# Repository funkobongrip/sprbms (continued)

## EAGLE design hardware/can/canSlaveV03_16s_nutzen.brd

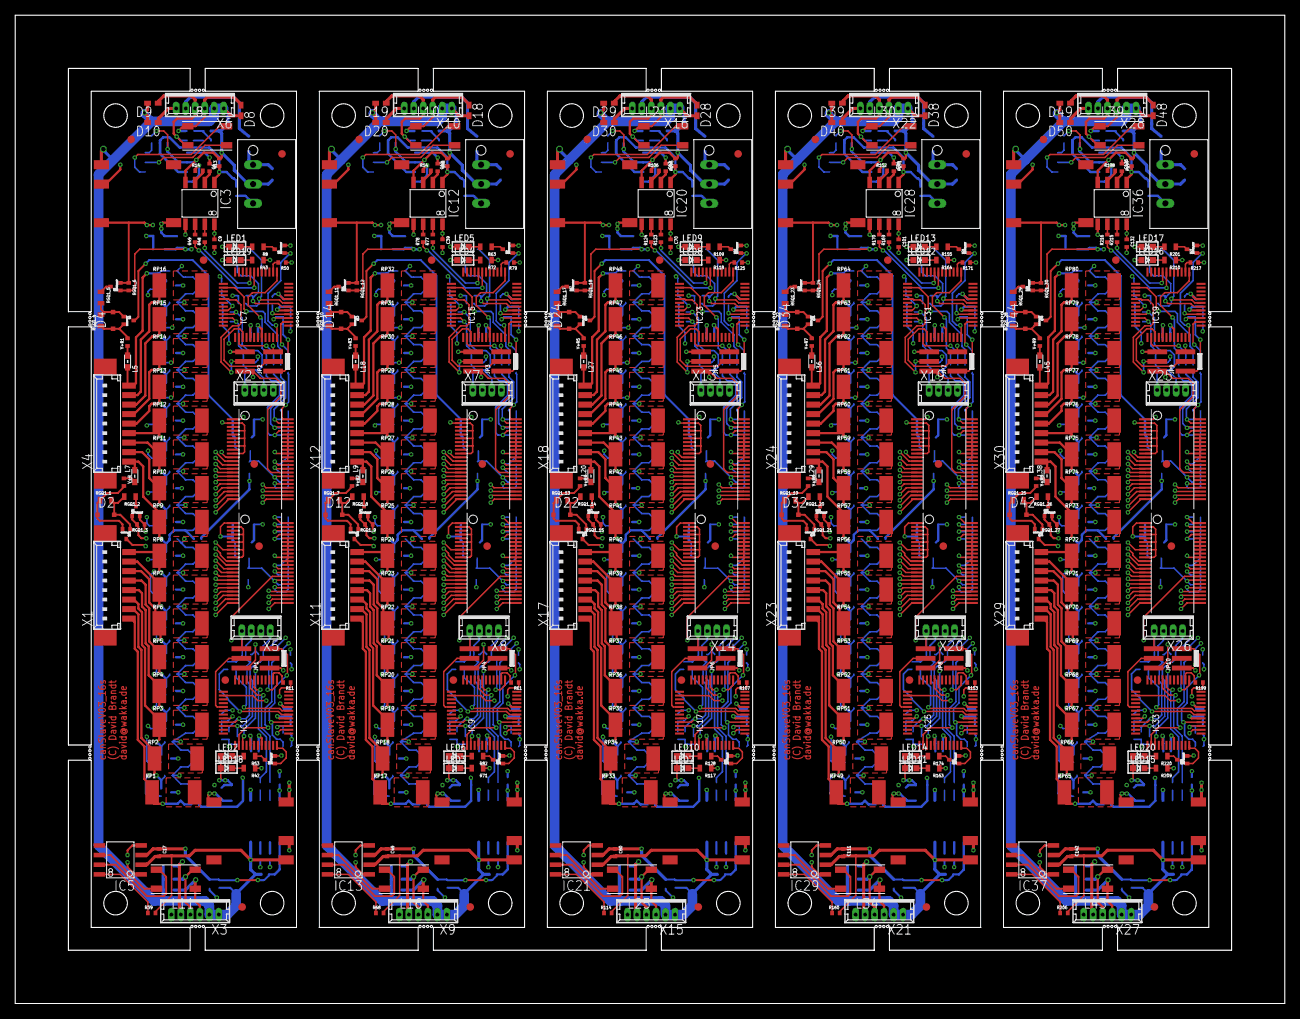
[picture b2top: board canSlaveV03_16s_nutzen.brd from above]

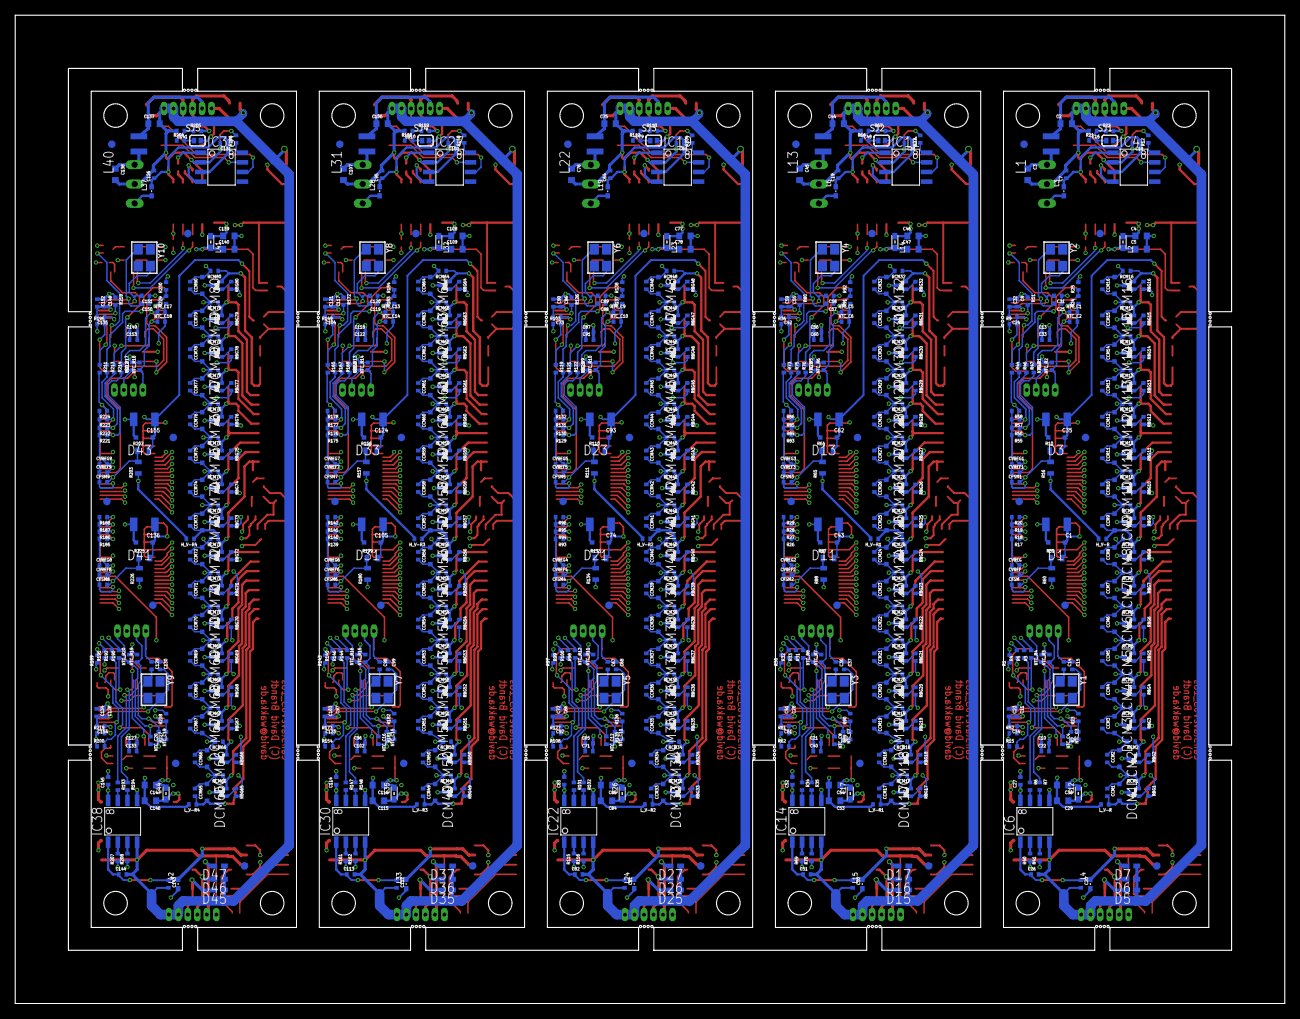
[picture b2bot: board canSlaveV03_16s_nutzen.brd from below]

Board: 4 copper layers, 167.0 x 130.0 mm, 1310 parts (905 on the bottom side), 895 nets.

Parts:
C1, C35, C43, C62, C74, C93, C105, C124, C136, C155: 10u,50V; C1206
C2, C3, C4, C5, C29, C30, C44, C45, C46, C47, C53, C54, C75, C76, C77, C78, C84, C85, C106, C107, C108, C109, C115, C116, C137, C138, C139, C140, C146, C147: 10u,50V; C0603
C6, C9, C12, C17, C18, C22, C23, C24, C26, C27, C32, C33, C34, C38, C39, C40, C41, C42, C49, C51, C52, C59, C60, C61, C63, C69, C70, C71, C72, C73, C80, C82, C83, C90, C91, C92, C94, C100, C101, C102, C103, C104, C111, C113, C114, C121, C122, C123, C125, C131, C132, C133, C134, C135, C142, C144, C145, C152, C153, C154: 100n; C0402
C7, C19, C20, C50, C64, C81, C95, C112, C126, C143: 1u; C0402
C8, C10, C11, C13, C21, C28, C55, C56, C65, C66, C86, C87, C96, C97, C117, C118, C127, C128, C148, C149: 10n; C0402
C14, C15, C25, C31, C36, C37, C57, C58, C67, C68, C88, C89, C98, C99, C119, C120, C129, C130, C150, C151: 18p; C0402
C16, C48, C79, C110, C141: 47n; C0402
CCM1, CCM2, CCM3, CCM4, CCM5, CCM6, CCM7, CCM8, CCM9, CCM10, CCM11, CCM12, CCM13, CCM14, CCM15, CCM16, CCM17, CCM18, CCM19, CCM20, CCM21, CCM22, CCM23, CCM24, CCM25, CCM26, CCM27, CCM28, CCM29, CCM30, CCM31, CCM32, CCM33, CCM34, CCM35, CCM36, CCM37, CCM38, CCM39, CCM40, CCM41, CCM42, CCM43, CCM44, CCM45, CCM46, CCM47, CCM48, CCM49, CCM50, CCM51, CCM52, CCM53, CCM54, CCM55, CCM56, CCM57, CCM58, CCM59, CCM60, CCM61, CCM62, CCM63, CCM64, CCM65, CCM66, CCM67, CCM68, CCM69, CCM70, CCM71, CCM72, CCM73, CCM74, CCM75, CCM76, CCM77, CCM78, CCM79, CCM80: 100n; C0402
CFSM, CFSM1, CFSM2, CFSM3, CFSM4, CFSM5, CFSM6, CFSM7, CFSM8, CFSM9: 1u; C0402
CVREF, CVREF1, CVREF2, CVREF3, CVREF4, CVREF5, CVREF6, CVREF7, CVREF8, CVREF9: 1u; C0402
CVREG, CVREG1, CVREG2, CVREG3, CVREG4, CVREG5, CVREG6, CVREG7, CVREG8, CVREG9: 1u; C0402
D1, D3, D11, D13, D21, D23, D31, D33, D41, D43: 40V; SOD323-R
D2, D4, D12, D14, D22, D24, D32, D34, D42, D44: 12V; SOD323-R
D5, D6, D7, D8, D9, D10, D15, D16, D17, D18, D19, D20, D25, D26, D27, D28, D29, D30, D35, D36, D37, D38, D39, D40, D45, D46, D47, D48, D49, D50: WE-VE_0402; WESURGE_0402
DCDC1, DCDC2, DCDC3, DCDC4, DCDC5, DCDC6, DCDC7, DCDC8, DCDC9, DCDC10: TES 1-0510; ISF
DCIN, DCIN1, DCIN2, DCIN3, DCIN4: TSR 1-2450; TSR1
DCM1, DCM2, DCM3, DCM4, DCM5, DCM6, DCM7, DCM8, DCM9, DCM10, DCM11, DCM12, DCM13, DCM14, DCM15, DCM16, DCM17, DCM18, DCM19, DCM20, DCM21, DCM22, DCM23, DCM24, DCM25, DCM26, DCM27, DCM28, DCM29, DCM30, DCM31, DCM32, DCM33, DCM34, DCM35, DCM36, DCM37, DCM38, DCM39, DCM40, DCM41, DCM42, DCM43, DCM44, DCM45, DCM46, DCM47, DCM48, DCM49, DCM50, DCM51, DCM52, DCM53, DCM54, DCM55, DCM56, DCM57, DCM58, DCM59, DCM60, DCM61, DCM62, DCM63, DCM64, DCM65, DCM66, DCM67, DCM68, DCM69, DCM70, DCM71, DCM72, DCM73, DCM74, DCM75, DCM76, DCM77, DCM78, DCM79, DCM80: 7.5; SOD323-R
FID1, FID2, FID3, FID4, FID5, FID6, FID7, FID8, FID9, FID10, FID11, FID12, FID13, FID14, FID15, FID16, FID17, FID18, FID19, FID20, FID21, FID22, FID23, FID24, FID25, FID26, FID27, FID28, FID29, FID30, FID31, FID32, FID33, FID34, FID35, FID36, FID37, FID38, FID39, FID40, FID41, FID42, FID43, FID44, FID45, FID46, FID47, FID48, FID49, FID50, FID51, FID52, FID53, FID54, FID55, FID56, FID57, FID58, FID59, FID60, FID61, FID62, FID63, FID64, FID65, FID66, FID67, FID68, FID69, FID70: FIDUCIAL""; FIDUCIAL_1MM
H_V-R, H_V-R1, H_V-R2, H_V-R3, H_V-R4: 100; R0402
IC1, IC7, IC9, IC15, IC17, IC23, IC25, IC31, IC33, IC39: LPC11C1X; LQFP48
IC2, IC8, IC10, IC16, IC18, IC24, IC26, IC32, IC34, IC40: LTC6803-4; 44SSOP
IC3, IC6, IC12, IC14, IC20, IC22, IC28, IC30, IC36, IC38: ADUM1201; SO-8
IC4, IC5, IC11, IC13, IC19, IC21, IC27, IC29, IC35, IC37: MCP2551; SO-8
JP1, JP2, JP3, JP4, JP5, JP6, JP7, JP8, JP9, JP10: 2X03_1.27MM_SMT
L1, L13, L22, L31, L40: WE-PMI_1008
L2, L5, L7, L9, L12, L14, L17, L18, L20, L23, L26, L27, L29, L32, L35, L36, L38, L41, L44, L45: WE-CBF_0603; 0603
L3, L4, L6, L15, L19, L24, L28, L33, L37, L42: WE-CBF_0402; 0402
L8, L10, L11, L16, L21, L25, L30, L34, L39, L43: WE-SL1
LED1, LED2, LED3, LED4, LED5, LED6, LED7, LED8, LED9, LED10, LED11, LED12, LED13, LED14, LED15, LED16, LED17, LED18, LED19, LED20: CHIPLED_0603
L_V-R, L_V-R1, L_V-R2, L_V-R3, L_V-R4: 100; R0402
NTC_C1, NTC_C2, NTC_C3, NTC_C4, NTC_C5, NTC_C6, NTC_C7, NTC_C8, NTC_C9, NTC_C10, NTC_C11, NTC_C12, NTC_C13, NTC_C14, NTC_C15, NTC_C16, NTC_C17, NTC_C18, NTC_C19, NTC_C20: 100n; C0402
NTC_R1, NTC_R2, NTC_R3, NTC_R4, NTC_R5, NTC_R6, NTC_R7, NTC_R8, NTC_R9, NTC_R10, NTC_R11, NTC_R12, NTC_R13, NTC_R14, NTC_R15, NTC_R16, NTC_R17, NTC_R18, NTC_R19, NTC_R20: 1k; R0402
Q1, Q6, Q8, Q12, Q14, Q18, Q20, Q24, Q26, Q30: BSS84AKT; SOT416
Q2, Q3, Q4, Q5, Q7, Q9, Q10, Q11, Q13, Q15, Q16, Q17, Q19, Q21, Q22, Q23, Q25, Q27, Q28, Q29: 2N7002BKT; SOT416
QB1, QB2, QB3, QB4, QB5, QB6, QB7, QB8, QB9, QB10, QB11, QB12, QB13, QB14, QB15, QB16, QB17, QB18, QB19, QB20, QB21, QB22, QB23, QB24, QB25, QB26, QB27, QB28, QB29, QB30, QB31, QB32, QB33, QB34, QB35, QB36, QB37, QB38, QB39, QB40, QB41, QB42, QB43, QB44, QB45, QB46, QB47, QB48, QB49, QB50, QB51, QB52, QB53, QB54, QB55, QB56, QB57, QB58, QB59, QB60, QB61, QB62, QB63, QB64, QB65, QB66, QB67, QB68, QB69, QB70, QB71, QB72, QB73, QB74, QB75, QB76, QB77, QB78, QB79, QB80: PMV65XP; SOT416
R1, R3, R4, R5, R6, R7, R13, R14, R30, R31, R32, R33, R34, R35, R38, R40, R41, R44, R45, R46, R47, R48, R49, R54, R69, R70, R73, R74, R75, R76, R77, R78, R97, R98, R99, R100, R101, R102, R105, R106, R115, R116, R119, R120, R121, R122, R123, R124, R143, R144, R145, R146, R147, R148, R151, R152, R161, R162, R165, R166, R167, R168, R169, R170, R189, R190, R191, R192, R193, R194, R197, R198, R207, R208, R211, R212, R213, R214, R215, R216: 100; R0402
R2, R23, R24, R25, R89, R90, R91, R92, R135, R136, R137, R138, R181, R182, R183, R184, R227, R228, R229, R230: VAR; R0402
R8, R42, R43, R53, R63, R71, R72, R82, R109, R117, R118, R128, R155, R163, R164, R174, R201, R209, R210, R220: 330; R0603
R9, R11, R15, R36, R50, R51, R52, R61, R62, R79, R80, R81, R103, R107, R108, R125, R126, R127, R149, R153, R154, R171, R172, R173, R195, R199, R200, R217, R218, R219: 10k; R0402
R10, R59, R64, R87, R110, R133, R156, R179, R202, R225: 332k0.1%; R0603
R12, R37, R39, R68, R104, R114, R150, R160, R196, R206: 1.5k; R0402
R16, R60, R65, R88, R111, R134, R157, R180, R203, R226: 20k0.1%; R0603
R17, R18, R20, R26, R27, R29, R55, R56, R58, R83, R84, R86, R93, R94, R96, R129, R130, R132, R139, R140, R142, R175, R176, R178, R185, R186, R188, R221, R222, R224: 1M; R0402
R19, R28, R57, R85, R95, R131, R141, R177, R187, R223: 4.7k; R0402
R21, R22, R66, R67, R112, R113, R158, R159, R204, R205: 60; R0402
RBG1, RBG2, RBG3, RBG4, RBG5, RBG6, RBG7, RBG8, RBG9, RBG10, RBG11, RBG12, RBG13, RBG14, RBG15, RBG16, RBG17, RBG18, RBG19, RBG20, RBG21, RBG22, RBG23, RBG24, RBG25, RBG26, RBG27, RBG28, RBG29, RBG30, RBG31, RBG32, RBG33, RBG34, RBG35, RBG36, RBG37, RBG38, RBG39, RBG40, RBG41, RBG42, RBG43, RBG44, RBG45, RBG46, RBG47, RBG48, RBG49, RBG50, RBG51, RBG52, RBG53, RBG54, RBG55, RBG56, RBG57, RBG58, RBG59, RBG60, RBG61, RBG62, RBG63, RBG64, RBG65, RBG66, RBG67, RBG68, RBG69, RBG70, RBG71, RBG72, RBG73, RBG74, RBG75, RBG76, RBG77, RBG78, RBG79, RBG80: 3.3k; R0402
RCM1, RCM2, RCM3, RCM4, RCM5, RCM6, RCM7, RCM8, RCM9, RCM10, RCM11, RCM12, RCM13, RCM14, RCM15, RCM16, RCM17, RCM18, RCM19, RCM20, RCM21, RCM22, RCM23, RCM24, RCM25, RCM26, RCM27, RCM28, RCM29, RCM30, RCM31, RCM32, RCM33, RCM34, RCM35, RCM36, RCM37, RCM38, RCM39, RCM40, RCM41, RCM42, RCM43, RCM44, RCM45, RCM46, RCM47, RCM48, RCM49, RCM50, RCM51, RCM52, RCM53, RCM54, RCM55, RCM56, RCM57, RCM58, RCM59, RCM60, RCM61, RCM62, RCM63, RCM64, RCM65, RCM66, RCM67, RCM68, RCM69, RCM70, RCM71, RCM72, RCM73, RCM74, RCM75, RCM76, RCM77, RCM78, RCM79, RCM80: 100; R0402
RGQ1_1, RGQ1_4, RGQ1_7, RGQ1_10, RGQ1_13, RGQ1_16, RGQ1_19, RGQ1_22, RGQ1_25, RGQ1_28: 1M,50V; R0603
RGQ1_2, RGQ1_5, RGQ1_8, RGQ1_11, RGQ1_14, RGQ1_17, RGQ1_20, RGQ1_23, RGQ1_26, RGQ1_29: 100k,50V; R0603
RGQ1_3, RGQ1_6, RGQ1_9, RGQ1_12, RGQ1_15, RGQ1_18, RGQ1_21, RGQ1_24, RGQ1_27, RGQ1_30: 1M; R0402
RP1, RP2, RP3, RP4, RP5, RP6, RP7, RP8, RP9, RP10, RP11, RP12, RP13, RP14, RP15, RP16, RP17, RP18, RP19, RP20, RP21, RP22, RP23, RP24, RP25, RP26, RP27, RP28, RP29, RP30, RP31, RP32, RP33, RP34, RP35, RP36, RP37, RP38, RP39, RP40, RP41, RP42, RP43, RP44, RP45, RP46, RP47, RP48, RP49, RP50, RP51, RP52, RP53, RP54, RP55, RP56, RP57, RP58, RP59, RP60, RP61, RP62, RP63, RP64, RP65, RP66, RP67, RP68, RP69, RP70, RP71, RP72, RP73, RP74, RP75, RP76, RP77, RP78, RP79, RP80: 22; R2512
SJ1, SJ2, SJ3, SJ4, SJ5: SOLDERJUMPER_REFLOW_NOPASTE_SMALL
V+R, V+R1, V+R2, V+R3, V+R4, V+R5, V+R6, V+R7, V+R8, V+R9: 100; R0402
X1, X11, X17, X23, X29: 53398-08
X2, X5, X7, X8, X13, X14, X19, X20, X25, X26: 53047-04
X3, X6, X9, X10, X15, X16, X21, X22, X27, X28: 53047-06
X4, X12, X18, X24, X30: 53398-09
Y1, Y2, Y3, Y4, Y5, Y6, Y7, Y8, Y9, Y10: CRYSTAL_3.2X2.5

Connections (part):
+3V3DCOUT: C4.1, DCDC1.5, L2.2
+3V3DCOUT1: C29.1, DCDC2.5, L12.2
+3V3DCOUT2: C46.1, DCDC3.5, L14.2
+3V3DCOUT3: C53.1, DCDC4.5, L17.2
+3V3DCOUT4: C77.1, DCDC5.5, L23.2
+3V3DCOUT5: C84.1, DCDC6.5, L26.2
+3V3DCOUT6: C108.1, DCDC7.5, L32.2
+3V3DCOUT7: C115.1, DCDC8.5, L35.2
+3V3DCOUT8: C139.1, DCDC9.5, L41.2
+3V3DCOUT9: C146.1, DCDC10.5, L44.2
BAL1: IC2.25, RBG1.2
BAL2: IC2.23, RBG2.2
BAL3: IC2.21, RBG3.2
BAL4: IC2.19, RBG4.2
BAL5: IC2.17, RBG5.2
BAL6: IC2.15, RBG6.2
BAL7: IC2.13, RBG7.2
BAL8: IC2.11, RBG8.2
BAL9: IC8.25, RBG9.2
BAL10: IC8.23, RBG10.2
BAL11: IC8.21, RBG11.2
BAL12: IC8.19, RBG12.2
BAL13: IC8.17, RBG13.2
BAL14: IC8.15, RBG14.2
BAL15: IC8.13, RBG15.2
BAL16: IC8.11, RBG16.2
BAL17: IC10.25, RBG17.2
BAL18: IC10.23, RBG18.2
BAL19: IC10.21, RBG19.2
BAL20: IC10.19, RBG20.2
BAL21: IC10.17, RBG21.2
BAL22: IC10.15, RBG22.2
BAL23: IC10.13, RBG23.2
BAL24: IC10.11, RBG24.2
BAL25: IC16.25, RBG25.2
BAL26: IC16.23, RBG26.2
BAL27: IC16.21, RBG27.2
BAL28: IC16.19, RBG28.2
BAL29: IC16.17, RBG29.2
BAL30: IC16.15, RBG30.2
BAL31: IC16.13, RBG31.2
BAL32: IC16.11, RBG32.2
BAL33: IC18.25, RBG33.2
BAL34: IC18.23, RBG34.2
BAL35: IC18.21, RBG35.2
BAL36: IC18.19, RBG36.2
BAL37: IC18.17, RBG37.2
BAL38: IC18.15, RBG38.2
BAL39: IC18.13, RBG39.2
BAL40: IC18.11, RBG40.2
BAL41: IC24.25, RBG41.2
BAL42: IC24.23, RBG42.2
BAL43: IC24.21, RBG43.2
BAL44: IC24.19, RBG44.2
BAL45: IC24.17, RBG45.2
BAL46: IC24.15, RBG46.2
BAL47: IC24.13, RBG47.2
BAL48: IC24.11, RBG48.2
BAL49: IC26.25, RBG49.2
BAL50: IC26.23, RBG50.2
BAL51: IC26.21, RBG51.2
BAL52: IC26.19, RBG52.2
BAL53: IC26.17, RBG53.2
BAL54: IC26.15, RBG54.2
BAL55: IC26.13, RBG55.2
BAL56: IC26.11, RBG56.2
BAL57: IC32.25, RBG57.2
BAL58: IC32.23, RBG58.2
BAL59: IC32.21, RBG59.2
BAL60: IC32.19, RBG60.2
BAL61: IC32.17, RBG61.2
BAL62: IC32.15, RBG62.2
BAL63: IC32.13, RBG63.2
BAL64: IC32.11, RBG64.2
BAL65: IC34.25, RBG65.2
BAL66: IC34.23, RBG66.2
BAL67: IC34.21, RBG67.2
BAL68: IC34.19, RBG68.2
BAL69: IC34.17, RBG69.2
BAL70: IC34.15, RBG70.2
BAL71: IC34.13, RBG71.2
BAL72: IC34.11, RBG72.2
BAL73: IC40.25, RBG73.2
BAL74: IC40.23, RBG74.2
BAL75: IC40.21, RBG75.2
BAL76: IC40.19, RBG76.2
BAL77: IC40.17, RBG77.2
BAL78: IC40.15, RBG78.2
BAL79: IC40.13, RBG79.2
BAL80: IC40.11, RBG80.2
C0: CCM1.2, DCM1.A, IC2.26, L_V-R.1, RP1.1, X1.8
C1: QB1.2, RCM1.1, RP2.1, X1.7
C1M: CCM1.1, CCM2.2, DCM1.C, DCM2.A, IC2.24, RCM1.2
C1M1: CCM17.1, CCM18.2, DCM17.C, DCM18.A, IC10.24, RCM17.2
C1M2: CCM33.1, CCM34.2, DCM33.C, DCM34.A, IC18.24, RCM33.2
C1M3: CCM49.1, CCM50.2, DCM49.C, DCM50.A, IC26.24, RCM49.2
C1M4: CCM65.1, CCM66.2, DCM65.C, DCM66.A, IC34.24, RCM65.2
C2: QB2.2, RCM2.1, RP3.1, X1.6
C2M: CCM2.1, CCM3.2, DCM2.C, DCM3.A, IC2.22, RCM2.2
C2M1: CCM18.1, CCM19.2, DCM18.C, DCM19.A, IC10.22, RCM18.2
C2M2: CCM34.1, CCM35.2, DCM34.C, DCM35.A, IC18.22, RCM34.2
C2M3: CCM50.1, CCM51.2, DCM50.C, DCM51.A, IC26.22, RCM50.2
C2M4: CCM66.1, CCM67.2, DCM66.C, DCM67.A, IC34.22, RCM66.2
C3: QB3.2, RCM3.1, RP4.1, X1.5
C3M: CCM3.1, CCM4.2, DCM3.C, DCM4.A, IC2.20, RCM3.2
C3M1: CCM19.1, CCM20.2, DCM19.C, DCM20.A, IC10.20, RCM19.2
C3M2: CCM35.1, CCM36.2, DCM35.C, DCM36.A, IC18.20, RCM35.2
C3M3: CCM51.1, CCM52.2, DCM51.C, DCM52.A, IC26.20, RCM51.2
C3M4: CCM67.1, CCM68.2, DCM67.C, DCM68.A, IC34.20, RCM67.2
C4: QB4.2, RCM4.1, RP5.1, X1.4
C4M: CCM4.1, CCM5.2, DCM4.C, DCM5.A, IC2.18, RCM4.2
C4M1: CCM20.1, CCM21.2, DCM20.C, DCM21.A, IC10.18, RCM20.2
C4M2: CCM36.1, CCM37.2, DCM36.C, DCM37.A, IC18.18, RCM36.2
C4M3: CCM52.1, CCM53.2, DCM52.C, DCM53.A, IC26.18, RCM52.2
C4M4: CCM68.1, CCM69.2, DCM68.C, DCM69.A, IC34.18, RCM68.2
C5: QB5.2, RCM5.1, RP6.1, X1.3
C5M: CCM5.1, CCM6.2, DCM5.C, DCM6.A, IC2.16, RCM5.2
C5M1: CCM21.1, CCM22.2, DCM21.C, DCM22.A, IC10.16, RCM21.2
C5M2: CCM37.1, CCM38.2, DCM37.C, DCM38.A, IC18.16, RCM37.2
C5M3: CCM53.1, CCM54.2, DCM53.C, DCM54.A, IC26.16, RCM53.2
C5M4: CCM69.1, CCM70.2, DCM69.C, DCM70.A, IC34.16, RCM69.2
C6: QB6.2, RCM6.1, RP7.1, X1.2
C6M: CCM6.1, CCM7.2, DCM6.C, DCM7.A, IC2.14, RCM6.2
C6M1: CCM22.1, CCM23.2, DCM22.C, DCM23.A, IC10.14, RCM22.2
C6M2: CCM38.1, CCM39.2, DCM38.C, DCM39.A, IC18.14, RCM38.2
C6M3: CCM54.1, CCM55.2, DCM54.C, DCM55.A, IC26.14, RCM54.2
C6M4: CCM70.1, CCM71.2, DCM70.C, DCM71.A, IC34.14, RCM70.2
C7: QB7.2, RCM7.1, RP8.1, X1.1
C7M: CCM7.1, CCM8.2, DCM7.C, DCM8.A, IC2.12, RCM7.2
C7M1: CCM23.1, CCM24.2, DCM23.C, DCM24.A, IC10.12, RCM23.2
C7M2: CCM39.1, CCM40.2, DCM39.C, DCM40.A, IC18.12, RCM39.2
C7M3: CCM55.1, CCM56.2, DCM55.C, DCM56.A, IC26.12, RCM55.2
C7M4: CCM71.1, CCM72.2, DCM71.C, DCM72.A, IC34.12, RCM71.2
C8: CCM9.2, DCM9.A, H_V-R.1, IC8.26, L7.1, QB8.2, RCM8.1, RP9.1, X4.9
C8M: CCM8.1, DCM8.C, IC2.2, IC2.4, IC2.6, IC2.8, IC2.10, RCM8.2
C8M1: CCM24.1, DCM24.C, IC10.2, IC10.4, IC10.6, IC10.8, IC10.10, RCM24.2
C8M2: CCM40.1, DCM40.C, IC18.2, IC18.4, IC18.6, IC18.8, IC18.10, RCM40.2
C8M3: CCM56.1, DCM56.C, IC26.2, IC26.4, IC26.6, IC26.8, IC26.10, RCM56.2
C8M4: CCM72.1, DCM72.C, IC34.2, IC34.4, IC34.6, IC34.8, IC34.10, RCM72.2
C9: QB9.2, RCM9.1, RP10.1, X4.8
C9M: CCM9.1, CCM10.2, DCM9.C, DCM10.A, IC8.24, RCM9.2
C9M1: CCM25.1, CCM26.2, DCM25.C, DCM26.A, IC16.24, RCM25.2
C9M2: CCM41.1, CCM42.2, DCM41.C, DCM42.A, IC24.24, RCM41.2
C9M3: CCM57.1, CCM58.2, DCM57.C, DCM58.A, IC32.24, RCM57.2
C9M4: CCM73.1, CCM74.2, DCM73.C, DCM74.A, IC40.24, RCM73.2
C10: QB10.2, RCM10.1, RP11.1, X4.7
C10M: CCM10.1, CCM11.2, DCM10.C, DCM11.A, IC8.22, RCM10.2
C10M1: CCM26.1, CCM27.2, DCM26.C, DCM27.A, IC16.22, RCM26.2
C10M2: CCM42.1, CCM43.2, DCM42.C, DCM43.A, IC24.22, RCM42.2
C10M3: CCM58.1, CCM59.2, DCM58.C, DCM59.A, IC32.22, RCM58.2
C10M4: CCM74.1, CCM75.2, DCM74.C, DCM75.A, IC40.22, RCM74.2
C11: QB11.2, RCM11.1, RP12.1, X4.6
C11M: CCM11.1, CCM12.2, DCM11.C, DCM12.A, IC8.20, RCM11.2
C11M1: CCM27.1, CCM28.2, DCM27.C, DCM28.A, IC16.20, RCM27.2
C11M2: CCM43.1, CCM44.2, DCM43.C, DCM44.A, IC24.20, RCM43.2
C11M3: CCM59.1, CCM60.2, DCM59.C, DCM60.A, IC32.20, RCM59.2
C11M4: CCM75.1, CCM76.2, DCM75.C, DCM76.A, IC40.20, RCM75.2
C12: QB12.2, RCM12.1, RP13.1, X4.5
C12M: CCM12.1, CCM13.2, DCM12.C, DCM13.A, IC8.18, RCM12.2
C12M1: CCM28.1, CCM29.2, DCM28.C, DCM29.A, IC16.18, RCM28.2
C12M2: CCM44.1, CCM45.2, DCM44.C, DCM45.A, IC24.18, RCM44.2
C12M3: CCM60.1, CCM61.2, DCM60.C, DCM61.A, IC32.18, RCM60.2
C12M4: CCM76.1, CCM77.2, DCM76.C, DCM77.A, IC40.18, RCM76.2
C13: QB13.2, RCM13.1, RP14.1, X4.4
C13M: CCM13.1, CCM14.2, DCM13.C, DCM14.A, IC8.16, RCM13.2
C13M1: CCM29.1, CCM30.2, DCM29.C, DCM30.A, IC16.16, RCM29.2
C13M2: CCM45.1, CCM46.2, DCM45.C, DCM46.A, IC24.16, RCM45.2
C13M3: CCM61.1, CCM62.2, DCM61.C, DCM62.A, IC32.16, RCM61.2
C13M4: CCM77.1, CCM78.2, DCM77.C, DCM78.A, IC40.16, RCM77.2
C14: QB14.2, RCM14.1, RP15.1, X4.3
C14M: CCM14.1, CCM15.2, DCM14.C, DCM15.A, IC8.14, RCM14.2
C14M1: CCM30.1, CCM31.2, DCM30.C, DCM31.A, IC16.14, RCM30.2
C14M2: CCM46.1, CCM47.2, DCM46.C, DCM47.A, IC24.14, RCM46.2
C14M3: CCM62.1, CCM63.2, DCM62.C, DCM63.A, IC32.14, RCM62.2
C14M4: CCM78.1, CCM79.2, DCM78.C, DCM79.A, IC40.14, RCM78.2
C15: QB15.2, RCM15.1, RP16.1, X4.2
C15M: CCM15.1, CCM16.2, DCM15.C, DCM16.A, IC8.12, RCM15.2
C15M1: CCM31.1, CCM32.2, DCM31.C, DCM32.A, IC16.12, RCM31.2
C15M2: CCM47.1, CCM48.2, DCM47.C, DCM48.A, IC24.12, RCM47.2
C15M3: CCM63.1, CCM64.2, DCM63.C, DCM64.A, IC32.12, RCM63.2
C15M4: CCM79.1, CCM80.2, DCM79.C, DCM80.A, IC40.12, RCM79.2
C16: L5.1, QB16.2, RCM16.1, X4.1
C16M: CCM16.1, DCM16.C, IC8.2, IC8.4, IC8.6, IC8.8, IC8.10, RCM16.2
C16M1: CCM32.1, DCM32.C, IC16.2, IC16.4, IC16.6, IC16.8, IC16.10, RCM32.2
C16M2: CCM48.1, DCM48.C, IC24.2, IC24.4, IC24.6, IC24.8, IC24.10, RCM48.2
C16M3: CCM64.1, DCM64.C, IC32.2, IC32.4, IC32.6, IC32.8, IC32.10, RCM64.2
C16M4: CCM80.1, DCM80.C, IC40.2, IC40.4, IC40.6, IC40.8, IC40.10, RCM80.2
C17: CCM17.2, DCM17.A, IC10.26, L_V-R1.1, RP17.1, X11.8
C18: CCM25.2, DCM25.A, H_V-R1.1, IC16.26, L9.1, QB24.2, RCM24.1, RP25.1, X12.9
C19: L18.1, QB32.2, RCM32.1, X12.1
C20: QB18.2, RCM18.1, RP19.1, X11.6
C21: QB17.2, RCM17.1, RP18.1, X11.7
C22: QB19.2, RCM19.1, RP20.1, X11.5
C23: QB20.2, RCM20.1, RP21.1, X11.4
C24: QB21.2, RCM21.1, RP22.1, X11.3
C25: QB22.2, RCM22.1, RP23.1, X11.2
C26: QB23.2, RCM23.1, RP24.1, X11.1
C27: QB25.2, RCM25.1, RP26.1, X12.8
C28: QB26.2, RCM26.1, RP27.1, X12.7
C29: QB27.2, RCM27.1, RP28.1, X12.6
C30: QB28.2, RCM28.1, RP29.1, X12.5
C31: QB29.2, RCM29.1, RP30.1, X12.4
C32: QB30.2, RCM30.1, RP31.1, X12.3
C33: QB31.2, RCM31.1, RP32.1, X12.2
C34: CCM33.2, DCM33.A, IC18.26, L_V-R2.1, RP33.1, X17.8
C35: CCM41.2, DCM41.A, H_V-R2.1, IC24.26, L20.1, QB40.2, RCM40.1, RP41.1, X18.9
C36: L27.1, QB48.2, RCM48.1, X18.1
C37: QB34.2, RCM34.1, RP35.1, X17.6
C38: QB33.2, RCM33.1, RP34.1, X17.7
C39: QB35.2, RCM35.1, RP36.1, X17.5
C40: QB36.2, RCM36.1, RP37.1, X17.4
C41: QB37.2, RCM37.1, RP38.1, X17.3
C42: QB38.2, RCM38.1, RP39.1, X17.2
C43: QB39.2, RCM39.1, RP40.1, X17.1
C44: QB41.2, RCM41.1, RP42.1, X18.8
C45: QB42.2, RCM42.1, RP43.1, X18.7
C46: QB43.2, RCM43.1, RP44.1, X18.6
C47: QB44.2, RCM44.1, RP45.1, X18.5
C48: QB45.2, RCM45.1, RP46.1, X18.4
C49: QB46.2, RCM46.1, RP47.1, X18.3
C50: QB47.2, RCM47.1, RP48.1, X18.2
C51: CCM49.2, DCM49.A, IC26.26, L_V-R3.1, RP49.1, X23.8
C52: CCM57.2, DCM57.A, H_V-R3.1, IC32.26, L29.1, QB56.2, RCM56.1, RP57.1, X24.9
C53: L36.1, QB64.2, RCM64.1, X24.1
C54: QB50.2, RCM50.1, RP51.1, X23.6
C55: QB49.2, RCM49.1, RP50.1, X23.7
C56: QB51.2, RCM51.1, RP52.1, X23.5
C57: QB52.2, RCM52.1, RP53.1, X23.4
C58: QB53.2, RCM53.1, RP54.1, X23.3
C59: QB54.2, RCM54.1, RP55.1, X23.2
C60: QB55.2, RCM55.1, RP56.1, X23.1
C61: QB57.2, RCM57.1, RP58.1, X24.8
C62: QB58.2, RCM58.1, RP59.1, X24.7
C63: QB59.2, RCM59.1, RP60.1, X24.6
C64: QB60.2, RCM60.1, RP61.1, X24.5
C65: QB61.2, RCM61.1, RP62.1, X24.4
C66: QB62.2, RCM62.1, RP63.1, X24.3
C67: QB63.2, RCM63.1, RP64.1, X24.2
C68: CCM65.2, DCM65.A, IC34.26, L_V-R4.1, RP65.1, X29.8
C69: CCM73.2, DCM73.A, H_V-R4.1, IC40.26, L38.1, QB72.2, RCM72.1, RP73.1, X30.9
C70: L45.1, QB80.2, RCM80.1, X30.1
C71: QB66.2, RCM66.1, RP67.1, X29.6
C72: QB65.2, RCM65.1, RP66.1, X29.7
C73: QB67.2, RCM67.1, RP68.1, X29.5
C74: QB68.2, RCM68.1, RP69.1, X29.4
C75: QB69.2, RCM69.1, RP70.1, X29.3
C76: QB70.2, RCM70.1, RP71.1, X29.2
C77: QB71.2, RCM71.1, RP72.1, X29.1
C78: QB73.2, RCM73.1, RP74.1, X30.8
C79: QB74.2, RCM74.1, RP75.1, X30.7
C80: QB75.2, RCM75.1, RP76.1, X30.6
C81: QB76.2, RCM76.1, RP77.1, X30.5
C82: QB77.2, RCM77.1, RP78.1, X30.4
C83: QB78.2, RCM78.1, RP79.1, X30.3
C84: QB79.2, RCM79.1, RP80.1, X30.2
CANH: D6.1, D9.2, L8.1, L11.1, SJ1.2, X3.3, X6.3
CANH1: D16.1, D19.2, L10.1, L16.1, SJ2.2, X9.3, X10.3
CANH2: D26.1, D29.2, L21.1, L25.1, SJ3.2, X15.3, X16.3
CANH3: D36.1, D39.2, L30.1, L34.1, SJ4.2, X21.3, X22.3
CANH4: D46.1, D49.2, L39.1, L43.1, SJ5.2, X27.3, X28.3
CANJ: R21.2, SJ1.1
CANJ1: R66.2, SJ2.1
CANJ2: R112.2, SJ3.1
CANJ3: R158.2, SJ4.1
CANJ4: R204.2, SJ5.1
CANL: D5.1, D8.2, L8.3, L11.3, R22.2, X3.4, X6.4
CANL1: D15.1, D18.2, L10.3, L16.3, R67.2, X9.4, X10.4
CANL2: D25.1, D28.2, L21.3, L25.3, R113.2, X15.4, X16.4
CANL3: D35.1, D38.2, L30.3, L34.3, R159.2, X21.4, X22.4
CANL4: D45.1, D48.2, L39.3, L43.3, R205.2, X27.4, X28.4
CANRX_U_H: IC7.19, R49.1
CANRX_U_H1: IC15.19, R78.1
CANRX_U_H2: IC23.19, R124.1
CANRX_U_H3: IC31.19, R170.1
CANRX_U_H4: IC39.19, R216.1
CANRX_U_L: IC1.19, R7.1
CANRX_U_L1: IC9.19, R35.1
CANRX_U_L2: IC17.19, R102.1
CANRX_U_L3: IC25.19, R148.1
CANRX_U_L4: IC33.19, R194.1
CANT: C16.1, R21.1, R22.1
CANT1: C48.1, R66.1, R67.1
CANT2: C79.1, R112.1, R113.1
CANT3: C110.1, R158.1, R159.1
CANT4: C141.1, R204.1, R205.1
CANTX_U_H: IC7.20, R48.1
CANTX_U_H1: IC15.20, R77.1
CANTX_U_H2: IC23.20, R123.1
CANTX_U_H3: IC31.20, R169.1
CANTX_U_H4: IC39.20, R215.1
CANTX_U_L: IC1.20, R6.1
CANTX_U_L1: IC9.20, R34.1
CANTX_U_L2: IC17.20, R101.1
CANTX_U_L3: IC25.20, R147.1
CANTX_U_L4: IC33.20, R193.1
CAR+5V: DCDC1.2, DCDC2.2, DCIN.3, L3.2, L4.2
CAR+5V1: DCDC3.2, DCDC4.2, DCIN1.3, L6.2, L15.2
CAR+5V2: DCDC5.2, DCDC6.2, DCIN2.3, L19.2, L24.2
CAR+5V3: DCDC7.2, DCDC8.2, DCIN3.3, L28.2, L33.2
CAR+5V4: DCDC9.2, DCDC10.2, DCIN4.3, L37.2, L42.2
CAR+5V_H: C6.1, C7.1, C18.1, IC3.1, IC4.3, L3.1
CAR+5V_H1: C12.1, C19.1, C38.1, IC11.3, IC12.1, L6.1
CAR+5V_H2: C63.1, C64.1, C69.1, IC19.3, IC20.1, L19.1
CAR+5V_H3: C94.1, C95.1, C100.1, IC27.3, IC28.1, L28.1
CAR+5V_H4: C125.1, C126.1, C131.1, IC35.3, IC36.1, L37.1
CAR+5V_LFILT: C17.1, C20.1, C26.1, IC5.3, IC6.1, L4.1
CAR+5V_LFILT1: C49.1, C50.1, C51.1, IC13.3, IC14.1, L15.1
CAR+5V_LFILT2: C80.1, C81.1, C82.1, IC21.3, IC22.1, L24.1
CAR+5V_LFILT3: C111.1, C112.1, C113.1, IC29.3, IC30.1, L33.1
CAR+5V_LFILT4: C142.1, C143.1, C144.1, IC37.3, IC38.1, L42.1
CAR+12V: C3.1, DCIN.1, L1.1
CAR+12V1: C45.1, DCIN1.1, L13.1
CAR+12V2: C76.1, DCIN2.1, L22.1
CAR+12V3: C107.1, DCIN3.1, L31.1
CAR+12V4: C138.1, DCIN4.1, L40.1
CAR+12VIN: C2.1, D7.1, D10.2, L1.2, X3.1, X3.2, X6.1, X6.2
CAR+12VIN1: C44.1, D17.1, D20.2, L13.2, X9.1, X9.2, X10.1, X10.2
CAR+12VIN2: C75.1, D27.1, D30.2, L22.2, X15.1, X15.2, X16.1, X16.2
CAR+12VIN3: C106.1, D37.1, D40.2, L31.2, X21.1, X21.2, X22.1, X22.2
CAR+12VIN4: C137.1, D47.1, D50.2, L40.2, X27.1, X27.2, X28.1, X28.2
CARGND: C2.2, C3.2, C6.2, C7.2, C16.2, C17.2, C18.2, C20.2, C26.2, D5.2, D6.2, D7.2, D8.1, D9.1, D10.1, DCDC1.1, DCDC2.1, DCIN.2, IC3.4, IC4.2, IC5.2, IC6.4, R12.2, R39.2, X3.5, X3.6, X6.5, X6.6
CARGND1: C12.2, C19.2, C38.2, C44.2, C45.2, C48.2, C49.2, C50.2, C51.2, D15.2, D16.2, D17.2, D18.1, D19.1, D20.1, DCDC3.1, DCDC4.1, DCIN1.2, IC11.2, IC12.4, IC13.2, IC14.4, R37.2, R68.2, X9.5, X9.6, X10.5, X10.6
CARGND2: C63.2, C64.2, C69.2, C75.2, C76.2, C79.2, C80.2, C81.2, C82.2, D25.2, D26.2, D27.2, D28.1, D29.1, D30.1, DCDC5.1, DCDC6.1, DCIN2.2, IC19.2, IC20.4, IC21.2, IC22.4, R104.2, R114.2, X15.5, X15.6, X16.5, X16.6
CARGND3: C94.2, C95.2, C100.2, C106.2, C107.2, C110.2, C111.2, C112.2, C113.2, D35.2, D36.2, D37.2, D38.1, D39.1, D40.1, DCDC7.1, DCDC8.1, DCIN3.2, IC27.2, IC28.4, IC29.2, IC30.4, R150.2, R160.2, X21.5, X21.6, X22.5, X22.6
CARGND4: C125.2, C126.2, C131.2, C137.2, C138.2, C141.2, C142.2, C143.2, C144.2, D45.2, D46.2, D47.2, D48.1, D49.1, D50.1, DCDC9.1, DCDC10.1, DCIN4.2, IC35.2, IC36.4, IC37.2, IC38.4, R196.2, R206.2, X27.5, X27.6, X28.5, X28.6
CR1: QB1.3, RP1.2
CR2: QB2.3, RP2.2
CR3: QB3.3, RP3.2
CR4: QB4.3, RP4.2
CR5: QB5.3, RP5.2
CR6: QB6.3, RP6.2
CR7: QB7.3, RP7.2
CR8: QB8.3, RP8.2
CR9: QB9.3, RP9.2
CR10: QB10.3, RP10.2
CR11: QB11.3, RP11.2
CR12: QB12.3, RP12.2
CR13: QB13.3, RP13.2
CR14: QB14.3, RP14.2
CR15: QB15.3, RP15.2
CR16: QB16.3, RP16.2
CR17: QB17.3, RP17.2
CR18: QB18.3, RP18.2
CR19: QB19.3, RP19.2
CR20: QB20.3, RP20.2
CR21: QB21.3, RP21.2
CR22: QB22.3, RP22.2
CR23: QB23.3, RP23.2
CR24: QB24.3, RP24.2
CR25: QB25.3, RP25.2
CR26: QB26.3, RP26.2
CR27: QB27.3, RP27.2
CR28: QB28.3, RP28.2
CR29: QB29.3, RP29.2
CR30: QB30.3, RP30.2
CR31: QB31.3, RP31.2
CR32: QB32.3, RP32.2
CR33: QB33.3, RP33.2
CR34: QB34.3, RP34.2
CR35: QB35.3, RP35.2
CR36: QB36.3, RP36.2
CR37: QB37.3, RP37.2
CR38: QB38.3, RP38.2
CR39: QB39.3, RP39.2
CR40: QB40.3, RP40.2
CR41: QB41.3, RP41.2
CR42: QB42.3, RP42.2
CR43: QB43.3, RP43.2
CR44: QB44.3, RP44.2
CR45: QB45.3, RP45.2
CR46: QB46.3, RP46.2
CR47: QB47.3, RP47.2
CR48: QB48.3, RP48.2
CR49: QB49.3, RP49.2
CR50: QB50.3, RP50.2
CR51: QB51.3, RP51.2
CR52: QB52.3, RP52.2
CR53: QB53.3, RP53.2
CR54: QB54.3, RP54.2
CR55: QB55.3, RP55.2
CR56: QB56.3, RP56.2
CR57: QB57.3, RP57.2
CR58: QB58.3, RP58.2
CR59: QB59.3, RP59.2
CR60: QB60.3, RP60.2
CR61: QB61.3, RP61.2
CR62: QB62.3, RP62.2
CR63: QB63.3, RP63.2
CR64: QB64.3, RP64.2
CR65: QB65.3, RP65.2
CR66: QB66.3, RP66.2
CR67: QB67.3, RP67.2
CR68: QB68.3, RP68.2
CR69: QB69.3, RP69.2
CR70: QB70.3, RP70.2
CR71: QB71.3, RP71.2
CR72: QB72.3, RP72.2
CR73: QB73.3, RP73.2
CR74: QB74.3, RP74.2
CR75: QB75.3, RP75.2
CR76: QB76.3, RP76.2
CR77: QB77.3, RP77.2
CR78: QB78.3, RP78.2
CR79: QB79.3, RP79.2
CR80: QB80.3, RP80.2
H+3V1: C39.1, C47.1, C55.1, C56.1, C59.1, C60.1, IC12.8, IC15.8, IC15.44, IC16.30, JP3.2, L14.1, LED4.A, LED5.A, NTC_R5.2, NTC_R6.2, Q11.1, R36.1, R80.1, R92.2, RGQ1_12.2
H+3V2: C70.1, C78.1, C86.1, C87.1, C90.1, C91.1, IC20.8, IC23.8, IC23.44, IC24.30, JP5.2, L23.1, LED8.A, LED9.A, NTC_R9.2, NTC_R10.2, Q17.1, R103.1, R126.1, R138.2, RGQ1_18.2
H+3V3: C5.1, C8.1, C9.1, C13.1, C32.1, C33.1, IC3.8, IC7.8, IC7.44, IC8.30, JP2.2, L2.1, LED1.A, LED19.A, NTC_R1.2, NTC_R2.2, Q5.1, R9.1, R25.2, R51.1, RGQ1_6.2
H+3V4: C101.1, C109.1, C117.1, C118.1, C121.1, C122.1, IC28.8, IC31.8, IC31.44, IC32.30, JP7.2, L32.1, LED12.A, LED13.A, NTC_R13.2, NTC_R14.2, Q23.1, R149.1, R172.1, R184.2, RGQ1_24.2
H+3V5: C132.1, C140.1, C148.1, C149.1, C152.1, C153.1, IC36.8, IC39.8, IC39.44, IC40.30, JP9.2, L41.1, LED16.A, LED17.A, NTC_R17.2, NTC_R18.2, Q29.1, R195.1, R218.1, R230.2, RGQ1_30.2
HCANHL: IC4.7, L8.5
HCANHL1: IC11.7, L10.5
HCANHL2: IC19.7, L21.5
HCANHL3: IC27.7, L30.5
HCANHL4: IC35.7, L39.5
HCANLL: IC4.6, L8.4
HCANLL1: IC11.6, L10.4
HCANLL2: IC19.6, L21.4
HCANLL3: IC27.6, L30.4
HCANLL4: IC35.6, L39.4
HGND: C4.2, C5.2, C8.2, C9.2, C13.2, C24.2, C25.1, C31.1, C32.2, C33.2, C35.2, CFSM1.1, CVREF1.1, CVREG1.1, D3.A, DCDC1.4, H_V-R.2, IC3.5, IC7.5, IC7.41, IC8.27, IC8.33, IC8.34, IC8.35, IC8.36, IC8.37, IC8.38, IC8.39, IC8.40, JP2.6, NTC_C1.2, NTC_C2.2, Q3.2, Q5.2, R16.1, R24.1, R43.1, R50.1, RGQ1_6.1, X2.1, X2.3
HGND1: C39.2, C42.2, C46.2, C47.2, C55.2, C56.2, C57.1, C58.1, C59.2, C60.2, C62.2, CFSM3.1, CVREF3.1, CVREG3.1, D13.A, DCDC3.4, H_V-R1.2, IC12.5, IC15.5, IC15.41, IC16.27, IC16.33, IC16.34, IC16.35, IC16.36, IC16.37, IC16.38, IC16.39, IC16.40, JP3.6, NTC_C5.2, NTC_C6.2, Q9.2, Q11.2, R65.1, R72.1, R79.1, R91.1, RGQ1_12.1, X7.1, X7.3
HGND2: C70.2, C73.2, C77.2, C78.2, C86.2, C87.2, C88.1, C89.1, C90.2, C91.2, C93.2, CFSM5.1, CVREF5.1, CVREG5.1, D23.A, DCDC5.4, H_V-R2.2, IC20.5, IC23.5, IC23.41, IC24.27, IC24.33, IC24.34, IC24.35, IC24.36, IC24.37, IC24.38, IC24.39, IC24.40, JP5.6, NTC_C9.2, NTC_C10.2, Q15.2, Q17.2, R111.1, R118.1, R125.1, R137.1, RGQ1_18.1, X13.1, X13.3
HGND3: C101.2, C104.2, C108.2, C109.2, C117.2, C118.2, C119.1, C120.1, C121.2, C122.2, C124.2, CFSM7.1, CVREF7.1, CVREG7.1, D33.A, DCDC7.4, H_V-R3.2, IC28.5, IC31.5, IC31.41, IC32.27, IC32.33, IC32.34, IC32.35, IC32.36, IC32.37, IC32.38, IC32.39, IC32.40, JP7.6, NTC_C13.2, NTC_C14.2, Q21.2, Q23.2, R157.1, R164.1, R171.1, R183.1, RGQ1_24.1, X19.1, X19.3
HGND4: C132.2, C135.2, C139.2, C140.2, C148.2, C149.2, C150.1, C151.1, C152.2, C153.2, C155.2, CFSM9.1, CVREF9.1, CVREG9.1, D43.A, DCDC9.4, H_V-R4.2, IC36.5, IC39.5, IC39.41, IC40.27, IC40.33, IC40.34, IC40.35, IC40.36, IC40.37, IC40.38, IC40.39, IC40.40, JP9.6, NTC_C17.2, NTC_C18.2, Q27.2, Q29.2, R203.1, R210.1, R217.1, R229.1, RGQ1_30.1, X25.1, X25.3
H_!RESET: C24.1, IC7.3, JP2.1, R9.2
H_!RESET1: C42.1, IC15.3, JP3.1, R36.2
H_!RESET2: C73.1, IC23.3, JP5.1, R103.2
H_!RESET3: C104.1, IC31.3, JP7.1, R149.2
H_!RESET4: C135.1, IC39.3, JP9.1, R195.2
H_AD1: IC7.33, NTC_C1.1, NTC_R1.1, X2.2
H_AD2: IC7.34, NTC_C2.1, NTC_R2.1, X2.4
H_AD3: IC15.33, NTC_C5.1, NTC_R5.1, X7.2
H_AD4: IC15.34, NTC_C6.1, NTC_R6.1, X7.4
H_AD5: IC23.33, NTC_C9.1, NTC_R9.1, X13.2
H_AD6: IC23.34, NTC_C10.1, NTC_R10.1, X13.4
H_AD7: IC31.33, NTC_C13.1, NTC_R13.1, X19.2
H_AD8: IC31.34, NTC_C14.1, NTC_R14.1, X19.4
H_AD9: IC39.33, NTC_C17.1, NTC_R17.1, X25.2
H_AD10: IC39.34, NTC_C18.1, NTC_R18.1, X25.4
H_ADR: IC7.32, R24.2, R25.1
H_ADR1: IC15.32, R91.2, R92.1
H_ADR2: IC23.32, R137.2, R138.1
H_ADR3: IC31.32, R183.2, R184.1
H_ADR4: IC39.32, R229.2, R230.1
H_CANRX: IC3.6, R49.2
H_CANRX1: IC12.6, R78.2
H_CANRX2: IC20.6, R124.2
H_CANRX3: IC28.6, R170.2
H_CANRX4: IC36.6, R216.2
H_CANTX: IC3.7, R48.2
H_CANTX1: IC12.7, R77.2
H_CANTX2: IC20.7, R123.2
H_CANTX3: IC28.7, R169.2
H_CANTX4: IC36.7, R215.2
H_CAR_CANRX: IC3.3, R14.2
H_CAR_CANRX1: IC12.3, R54.2
H_CAR_CANRX2: IC20.3, R106.2
H_CAR_CANRX3: IC28.3, R152.2
H_CAR_CANRX4: IC36.3, R198.2
H_CAR_CANRX_T: IC4.4, R14.1
H_CAR_CANRX_T1: IC11.4, R54.1
H_CAR_CANRX_T2: IC19.4, R106.1
H_CAR_CANRX_T3: IC27.4, R152.1
H_CAR_CANRX_T4: IC35.4, R198.1
H_CAR_CANTX: IC3.2, R13.2
H_CAR_CANTX1: IC12.2, R38.2
H_CAR_CANTX2: IC20.2, R105.2
H_CAR_CANTX3: IC28.2, R151.2
H_CAR_CANTX4: IC36.2, R197.2
H_CAR_CANTX_T: IC4.1, R13.1
H_CAR_CANTX_T1: IC11.1, R38.1
H_CAR_CANTX_T2: IC19.1, R105.1
H_CAR_CANTX_T3: IC27.1, R151.1
H_CAR_CANTX_T4: IC35.1, R197.1
H_CSB: IC8.44, R44.2, R58.1
H_CSB1: IC16.44, R73.2, R86.1
H_CSB2: IC24.44, R119.2, R132.1
H_CSB3: IC32.44, R165.2, R178.1
H_CSB4: IC40.44, R211.2, R224.1
H_FSM: CFSM1.2, IC8.29, R10.1, R16.2
H_FSM1: CFSM3.2, IC16.29, R64.1, R65.2
H_FSM2: CFSM5.2, IC24.29, R110.1, R111.2
H_FSM3: CFSM7.2, IC32.29, R156.1, R157.2
H_FSM4: CFSM9.2, IC40.29, R202.1, R203.2
H_ISP_CAN: IC7.14, R50.2
H_ISP_CAN1: IC15.14, R79.2
H_ISP_CAN2: IC23.14, R125.2
H_ISP_CAN3: IC31.14, R171.2
H_ISP_CAN4: IC39.14, R217.2
H_ISP_ENTER: IC7.4, JP2.5, R51.2
H_ISP_ENTER1: IC15.4, JP3.5, R80.2
H_ISP_ENTER2: IC23.4, JP5.5, R126.2
H_ISP_ENTER3: IC31.4, JP7.5, R172.2
H_ISP_ENTER4: IC39.4, JP9.5, R218.2
H_LED: IC7.48, Q3.1
H_LED1: IC15.48, Q9.1
H_LED2: IC23.48, Q15.1
H_LED3: IC31.48, Q21.1
H_LED4: IC39.48, Q27.1
H_MISO: IC7.26, R46.1
H_MISO1: IC15.26, R75.1
H_MISO2: IC23.26, R121.1
H_MISO3: IC31.26, R167.1
H_MISO4: IC39.26, R213.1
H_MOSI: IC7.38, R47.1
H_MOSI1: IC15.38, R76.1
H_MOSI2: IC23.38, R122.1
H_MOSI3: IC31.38, R168.1
H_MOSI4: IC39.38, R214.1
H_SCK: IC8.41, R45.2, R55.1
H_SCK1: IC7.13, R45.1
H_SCK2: IC16.41, R74.2, R83.1
H_SCK3: IC15.13, R74.1
H_SCK4: IC24.41, R120.2, R129.1
H_SCK5: IC23.13, R120.1
H_SCK6: IC32.41, R166.2, R175.1
H_SCK7: IC31.13, R166.1
H_SCK8: IC40.41, R212.2, R221.1
H_SCK9: IC39.13, R212.1
H_SDI: IC8.42, R47.2, R56.1
H_SDI1: IC16.42, R76.2, R84.1
H_SDI2: IC24.42, R122.2, R130.1
H_SDI3: IC32.42, R168.2, R176.1
H_SDI4: IC40.42, R214.2, R222.1
H_SDO: IC8.43, R46.2, R57.1
H_SDO1: IC16.43, R75.2, R85.1
H_SDO2: IC24.43, R121.2, R131.1
H_SDO3: IC32.43, R167.2, R177.1
H_SDO4: IC40.43, R213.2, R223.1
H_SSEL: IC7.2, R44.1
H_SSEL1: IC15.2, R73.1
H_SSEL2: IC23.2, R119.1
H_SSEL3: IC31.2, R165.1
H_SSEL4: IC39.2, R211.1
H_SWCLK: IC7.29, JP2.4
H_SWCLK1: IC15.29, JP3.4
H_SWCLK2: IC23.29, JP5.4
H_SWCLK3: IC31.29, JP7.4
H_SWCLK4: IC39.29, JP9.4
H_SWDIO: IC7.39, JP2.3
H_SWDIO1: IC15.39, JP3.3
H_SWDIO2: IC23.39, JP5.3
H_SWDIO3: IC31.39, JP7.3
H_SWDIO4: IC39.39, JP9.3
H_V+: C35.1, D3.C, IC8.1, Q6.3, R10.2
H_V+1: C62.1, D13.C, IC16.1, Q12.3, R64.2
H_V+2: C93.1, D23.C, IC24.1, Q18.3, R110.2
H_V+3: C124.1, D33.C, IC32.1, Q24.3, R156.2
H_V+4: C155.1, D43.C, IC40.1, Q30.3, R202.2
H_VREF: CVREF1.2, IC8.31
H_VREF1: CVREF3.2, IC16.31
H_VREF2: CVREF5.2, IC24.31
H_VREF3: CVREF7.2, IC32.31
H_VREF4: CVREF9.2, IC40.31
H_VREG: CVREG1.2, IC8.32, R55.2, R56.2, R57.2, R58.2
H_VREG1: CVREG3.2, IC16.32, R83.2, R84.2, R85.2, R86.2
H_VREG2: CVREG5.2, IC24.32, R129.2, R130.2, R131.2, R132.2
H_VREG3: CVREG7.2, IC32.32, R175.2, R176.2, R177.2, R178.2
H_VREG4: CVREG9.2, IC40.32, R221.2, R222.2, R223.2, R224.2
L+3V1: C21.1, C28.1, C40.1, C41.1, C52.1, C54.1, IC9.8, IC9.44, IC10.30, IC14.8, JP4.2, L17.1, LED3.A, LED6.A, NTC_R7.2, NTC_R8.2, Q7.1, R62.1, R81.1, R90.2, RGQ1_9.2
L+3V2: C65.1, C66.1, C71.1, C72.1, C83.1, C85.1, IC17.8, IC17.44, IC18.30, IC22.8, JP6.2, L26.1, LED7.A, LED10.A, NTC_R11.2, NTC_R12.2, Q13.1, R108.1, R127.1, R136.2, RGQ1_15.2
L+3V3: C10.1, C11.1, C22.1, C23.1, C27.1, C30.1, IC1.8, IC1.44, IC2.30, IC6.8, JP1.2, L12.1, LED2.A, LED18.A, NTC_R3.2, NTC_R4.2, Q2.1, R15.1, R23.2, R52.1, RGQ1_3.2
L+3V4: C96.1, C97.1, C102.1, C103.1, C114.1, C116.1, IC25.8, IC25.44, IC26.30, IC30.8, JP8.2, L35.1, LED11.A, LED14.A, NTC_R15.2, NTC_R16.2, Q19.1, R154.1, R173.1, R182.2, RGQ1_21.2
L+3V5: C127.1, C128.1, C133.1, C134.1, C145.1, C147.1, IC33.8, IC33.44, IC34.30, IC38.8, JP10.2, L44.1, LED15.A, LED20.A, NTC_R19.2, NTC_R20.2, Q25.1, R200.1, R219.1, R228.2, RGQ1_27.2
LCANHL: IC5.7, L11.5
LCANHL1: IC13.7, L16.5
LCANHL2: IC21.7, L25.5
LCANHL3: IC29.7, L34.5
LCANHL4: IC37.7, L43.5
LCANLL: IC5.6, L11.4
LCANLL1: IC13.6, L16.4
LCANLL2: IC21.6, L25.4
LCANLL3: IC29.6, L34.4
LCANLL4: IC37.6, L43.4
LED1C1: LED1.C, R8.2
LED1C2: LED2.C, R53.2
LED1C3: LED5.C, R63.2
LED1C4: LED6.C, R82.2
LED1C5: LED9.C, R109.2
LED1C6: LED10.C, R128.2
LED1C7: LED13.C, R155.2
LED1C8: LED14.C, R174.2
LED1C9: LED17.C, R201.2
LED1C10: LED20.C, R220.2
LGND: C1.2, C10.2, C11.2, C14.1, C15.1, C22.2, C23.2, C27.2, C29.2, C30.2, C34.2, CFSM.1, CVREF.1, CVREG.1, D1.A, DCDC2.4, IC1.5, IC1.41, IC2.27, IC2.33, IC2.34, IC2.35, IC2.36, IC2.37, IC2.38, IC2.39, IC2.40, IC6.5, JP1.6, L_V-R.2, NTC_C3.2, NTC_C4.2, Q2.2, Q4.2, R2.1, R11.1, R42.1, R60.1, RGQ1_3.1, X5.1, X5.3
LGND1: C21.2, C28.2, C36.1, C37.1, C40.2, C41.2, C43.2, C52.2, C53.2, C54.2, C61.2, CFSM2.1, CVREF2.1, CVREG2.1, D11.A, DCDC4.4, IC9.5, IC9.41, IC10.27, IC10.33, IC10.34, IC10.35, IC10.36, IC10.37, IC10.38, IC10.39, IC10.40, IC14.5, JP4.6, L_V-R1.2, NTC_C7.2, NTC_C8.2, Q7.2, Q10.2, R61.1, R71.1, R88.1, R89.1, RGQ1_9.1, X8.1, X8.3
LGND2: C65.2, C66.2, C67.1, C68.1, C71.2, C72.2, C74.2, C83.2, C84.2, C85.2, C92.2, CFSM4.1, CVREF4.1, CVREG4.1, D21.A, DCDC6.4, IC17.5, IC17.41, IC18.27, IC18.33, IC18.34, IC18.35, IC18.36, IC18.37, IC18.38, IC18.39, IC18.40, IC22.5, JP6.6, L_V-R2.2, NTC_C11.2, NTC_C12.2, Q13.2, Q16.2, R107.1, R117.1, R134.1, R135.1, RGQ1_15.1, X14.1, X14.3
LGND3: C96.2, C97.2, C98.1, C99.1, C102.2, C103.2, C105.2, C114.2, C115.2, C116.2, C123.2, CFSM6.1, CVREF6.1, CVREG6.1, D31.A, DCDC8.4, IC25.5, IC25.41, IC26.27, IC26.33, IC26.34, IC26.35, IC26.36, IC26.37, IC26.38, IC26.39, IC26.40, IC30.5, JP8.6, L_V-R3.2, NTC_C15.2, NTC_C16.2, Q19.2, Q22.2, R153.1, R163.1, R180.1, R181.1, RGQ1_21.1, X20.1, X20.3
LGND4: C127.2, C128.2, C129.1, C130.1, C133.2, C134.2, C136.2, C145.2, C146.2, C147.2, C154.2, CFSM8.1, CVREF8.1, CVREG8.1, D41.A, DCDC10.4, IC33.5, IC33.41, IC34.27, IC34.33, IC34.34, IC34.35, IC34.36, IC34.37, IC34.38, IC34.39, IC34.40, IC38.5, JP10.6, L_V-R4.2, NTC_C19.2, NTC_C20.2, Q25.2, Q28.2, R199.1, R209.1, R226.1, R227.1, RGQ1_27.1, X26.1, X26.3
L_!RESET: C34.1, IC1.3, JP1.1, R52.2
L_!RESET1: C61.1, IC9.3, JP4.1, R81.2
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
